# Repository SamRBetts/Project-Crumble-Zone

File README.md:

# Project-Crumble-Zone

Welcome to all version-controlled CAD for the ME capstone CanSat project!

Guidelines: 
<ul>
<li>Every assembly lives in a similarly-named folder containing itself + everything needed to construct it; this may include more assembly folders</li>
<li>Anything that is made from a single piece of material or single off-the-shelf component is a SLDPRT, anything else is a SLDASM</li>
<li>If you need a stock part, copy it or add it to the Github stock parts repo</li>
<li>Make subassemblies when a set of parts logically functions together; at minimum, anything that is glued together should be its own assembly, and anything that will be handled as a unit should be its own assembly (ex: the avbay should be one assembly) </li>
<li>File names should be snake case (like_this), folder names should be upper camel case (LikeThis)</li>
<li>Shared interface parts like couplers and screws should belong to the assembly that they are permanently attached to first; if it’s not obvious which side they should belong to, they should belong to the overarching assembly</li>
</ul>

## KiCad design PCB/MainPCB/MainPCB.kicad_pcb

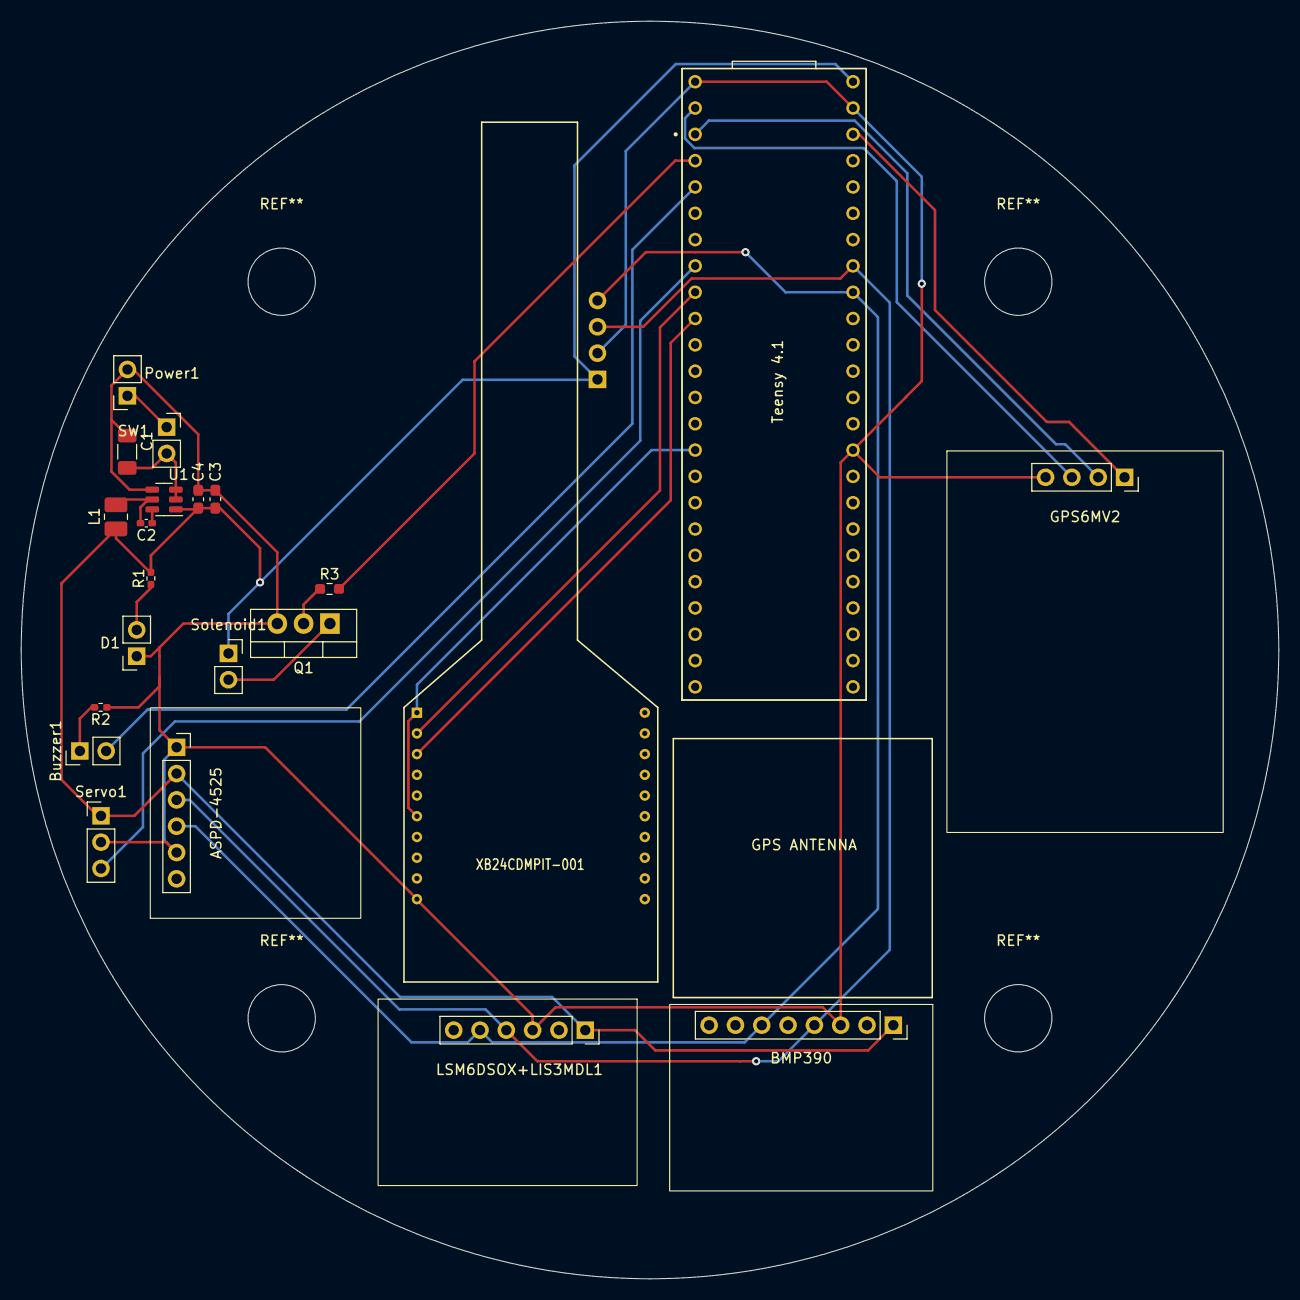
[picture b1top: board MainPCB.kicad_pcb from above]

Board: 2 copper layers, 121.4 x 121.4 mm, 23 parts (1 on the bottom side), 20 nets.

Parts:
ASPD-4525: Conn_01x06_Socket; PinSocket_1x06_P2.54mm_Vertical
BMP390: Conn_01x08_Socket; PinSocket_1x08_P2.54mm_Vertical
Buzzer1: Conn_01x02_Pin; PinHeader_1x02_P2.54mm_Vertical
C1: 10 uF; C_1206_3216Metric_Pad1.33x1.80mm_HandSolder
C2: 100 nF; C_0402_1005Metric_Pad0.74x0.62mm_HandSolder
C3, C4: 22 uF; C_0603_1608Metric_Pad1.08x0.95mm_HandSolder
D1: LED; PinSocket_1x02_P2.54mm_Vertical
GPS6MV2: Conn_01x04_Socket; PinSocket_1x04_P2.54mm_Vertical
L1: 4.7 uH; L_1008_2520Metric_Pad1.43x2.20mm_HandSolder
LSM6DSOX+LIS3MDL1: Conn_01x06_Socket; PinSocket_1x06_P2.54mm_Vertical
Power1: Conn_01x02_Pin; PinSocket_1x02_P2.54mm_Vertical
Q1: NMOS; TO-220-3_Vertical
R1: 100 kO; R_0402_1005Metric_Pad0.72x0.64mm_HandSolder
R2: 1 kO; R_0402_1005Metric_Pad0.72x0.64mm_HandSolder
R3: 2.1 kO; R_0603_1608Metric_Pad0.98x0.95mm_HandSolder
SEN291: Conn_01x04_Socket; PinSocket_1x04_P2.54mm_Vertical
SW1: SW_DIP_x01; PinSocket_1x02_P2.54mm_Vertical
Servo1: Conn_01x03_Pin; PinHeader_1x03_P2.54mm_Vertical
Solenoid1: Conn_01x02_Pin; PinSocket_1x02_P2.54mm_Vertical
TEENSY1: DEV-16771; MODULE_DEV-16771
U1: AP63205WU; TSOT-23-6
XBEE1: XB24CDMPIT-001; DIP-20

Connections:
+5V: ASPD-4525.2 (5V), BMP390.1 (VIN), C3.2, C4.2, L1.2, LSM6DSOX+LIS3MDL1.1 (Vin), R1.2, SEN291.1 (Vcc), Servo1.1, Solenoid1.1, TEENSY1.VIN, U1.1 (FB)
GND: ASPD-4525.1 (GND), ASPD-4525.5 (GND), BMP390.3 (GND), C1.2, C3.1, C4.1, D1.1 (K), GPS6MV2.4 (GND), LSM6DSOX+LIS3MDL1.3 (GND), Power1.2, Q1.3 (S), R2.1, SEN291.2 (GND), Servo1.2, TEENSY1.GND1 (GND), TEENSY1.GND2 (GND), TEENSY1.GND3 (GND), U1.4 (GND), XBEE1.10
unnamed: ASPD-4525.3 (SCL), BMP390.4 (SCL), LSM6DSOX+LIS3MDL1.4 (SCL), SEN291.3 (SCL), TEENSY1.19 (A5)
unnamed: ASPD-4525.4 (SDA), BMP390.6 (SDA), LSM6DSOX+LIS3MDL1.5 (SDA), SEN291.4 (SDA), TEENSY1.18 (A4)
unnamed: Buzzer1.1, R2.2
unnamed: Buzzer1.2, TEENSY1.3 (LRCLK2)
unnamed: D1.2 (A), R1.1
unnamed: GPS6MV2.2 (RX), TEENSY1.1 (TX1)
unnamed: GPS6MV2.3 (TX), TEENSY1.0 (RX1)
unnamed: GPS6MV2.1 (Vcc), TEENSY1.3.3V_1 (3.3V), TEENSY1.3.3V_2 (3.3V), XBEE1.1, XBEE1.6
unnamed: Power1.1, SW1.1
unnamed: Q1.1 (D), Solenoid1.2
unnamed: Q1.2 (G), R3.1
unnamed: Servo1.3, TEENSY1.6 (OUT1D)
unnamed: R3.2, TEENSY1.2 (OUT2)
unnamed: TEENSY1.7 (RX2), XBEE1.2
unnamed: TEENSY1.8 (TX2), XBEE1.3
unnamed: C2.1, U1.6 (BST)
unnamed: C1.1, SW1.2, U1.2 (EN), U1.3 (IN)
unnamed: C2.2, L1.1, U1.5 (SW)

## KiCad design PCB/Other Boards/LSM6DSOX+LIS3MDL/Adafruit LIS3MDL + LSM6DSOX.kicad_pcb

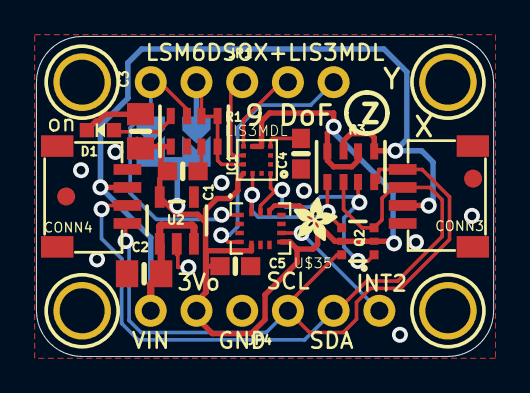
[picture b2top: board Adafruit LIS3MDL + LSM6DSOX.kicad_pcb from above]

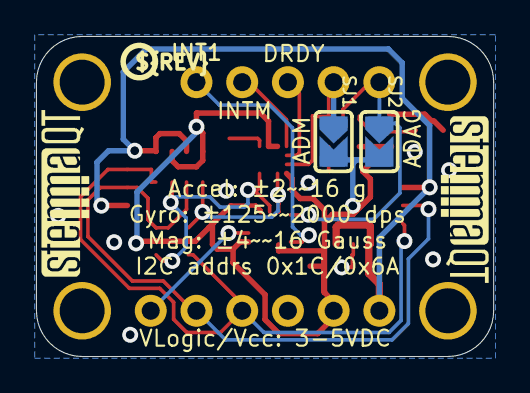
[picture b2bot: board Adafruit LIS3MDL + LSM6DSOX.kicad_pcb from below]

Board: 2 copper layers, 25.4 x 17.8 mm, 28 parts (5 on the bottom side), 15 nets.

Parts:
C1, C4: 0.1uF; 0603-NO
C2, C3: 10uF; 0805-NO
C5: 1uF; 0603-NO
CONN3, CONN4: STEMMA_I2C_QT; JST_SH4
D1: GREEN; CHIPLED_0603_NOOUTLINE
FID3, FID4: FIDUCIAL_1MM
IC1: LIS3MDL; LGA12_2X2MM
JP1: 1X05_ROUND_70
JP4: 1X06_ROUND_70
Q2: BSS138; SOT363
R1, R3: 10K; RESPACK_4X0603
SJ1, SJ2: SOLDERJUMPER_ARROW_NOPASTE
U2: AP2112K-3.3; SOT23-5
U$1, U$17, U$19, U$21: MOUNTINGHOLE2.5; MOUNTINGHOLE_2.5_PLATED
U$20: ADAFRUIT_2.5MM
U$25: PCBFEAT-REV-040
U$30, U$31: STEMMAQT
U$35: LSM6DSOX; LGA-14L

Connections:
3.3V: C1.1, C3.1, C5.1, IC1.5, IC1.6, IC1.10, JP4.2, Q2.2, Q2.5, R1.1, R3.2, R3.4, SJ1.2, SJ2.2, U2.5, U$35.5, U$35.8, U$35.12
ADAG: JP1.1, R1.7, SJ2.1, U$35.1
ADM: IC1.9, JP1.2, R1.4, R1.5, R1.6, SJ1.1
CAP: C4.1, IC1.4
DRDY: IC1.8, JP1.3
GND: C1.2, C2.2, C3.2, C4.2, C5.2, CONN3.1, CONN3.MT1, CONN3.MT2, CONN4.1, CONN4.MT1, CONN4.MT2, D1.C, IC1.2, IC1.3, IC1.12, JP4.3, R1.2, R1.3, U2.2, U$35.6, U$35.7
INT1: JP1.5, U$35.4
INT2: JP4.6, U$35.9
INTM: IC1.7, JP1.4
unnamed: D1.A, R1.8
SCL: CONN3.4, CONN4.4, JP4.4, Q2.6, R3.8
SCL_3V: IC1.1, Q2.1, R3.7, U$35.13
SDA: CONN3.3, CONN4.3, JP4.5, Q2.3, R3.6
SDA_3V: IC1.11, Q2.4, R3.5, U$35.14
VCC: C2.1, CONN3.2, CONN4.2, JP4.1, R3.1, R3.3, U2.1, U2.3

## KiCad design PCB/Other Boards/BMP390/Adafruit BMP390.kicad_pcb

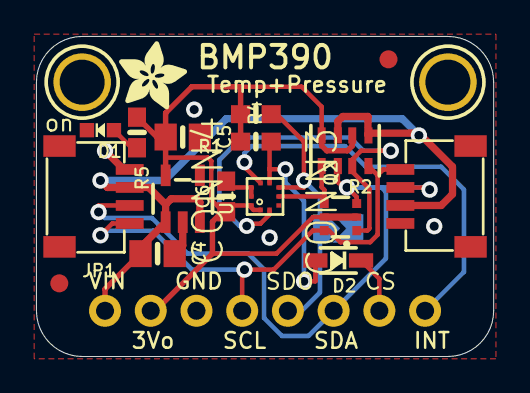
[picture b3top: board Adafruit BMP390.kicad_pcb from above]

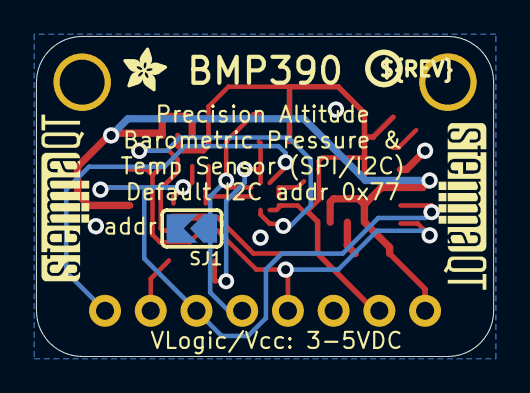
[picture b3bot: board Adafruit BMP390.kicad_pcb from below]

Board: 2 copper layers, 25.4 x 17.8 mm, 25 parts (5 on the bottom side), 12 nets.

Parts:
C4, C5: 10uF; 0805-NO
C6: 0.1uF; 0603-NO
CONN3, CONN4: STEMMA_I2C_QT; JST_SH4
D1: GREEN; CHIPLED_0603_NOOUTLINE
D2: 1N4148; SOD-323
FID3, FID4: FIDUCIAL_1MM
IC1: BMP388
JP1: 1X08_ROUND_70
Q2: BSS138; SOT363
R1, R4, R5: 10K; 0603-NO
R2: 10K; RESPACK_4X0603
SJ1: SOLDERJUMPER_ARROW_NOPASTE
U1: AP2112K-3.3; SOT23-5
U$2: ADAFRUIT_2.5MM
U$40, U$41: MOUNTINGHOLE2.5; MOUNTINGHOLE_2.5_PLATED
U$46: ADAFRUIT_3.5MM
U$47: PCBFEAT-REV-040
U$48, U$49: STEMMAQT

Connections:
3.3V: C5.1, C6.1, IC1.1, IC1.10, JP1.2, Q2.2, Q2.5, R1.2, R2.2, R2.4, R4.2, R5.1, U1.5
CS: D2.C, JP1.7
CS_3V: D2.A, IC1.6, R1.1
GND: C4.2, C5.2, C6.2, CONN3.1, CONN3.MT1, CONN3.MT2, CONN4.1, CONN4.MT1, CONN4.MT2, D1.C, IC1.3, IC1.8, IC1.9, JP1.3, SJ1.2, U1.2
INT: IC1.7, JP1.8
unnamed: D1.A, R5.2
SCK/SCL: CONN3.4, CONN4.4, JP1.4, Q2.6, R2.8
SCK_3V: IC1.2, Q2.1, R2.7
SDI/SDA: CONN3.3, CONN4.3, JP1.6, Q2.3, R2.6
SDI_3V: IC1.4, Q2.4, R2.5
SDO/ADR: IC1.5, JP1.5, R4.1, SJ1.1
VCC: C4.1, CONN3.2, CONN4.2, JP1.1, R2.1, R2.3, U1.1, U1.3

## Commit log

2023-10-04 Update README.md
    updated formatting guidelines
2023-10-04 Nose cone as heat shield design CAD
2023-10-09 Container with Servo Casing
2023-10-09 concept 1 body
2023-10-09 Slitv2assem unfinished
2023-10-09 slitv2 finished
2023-10-10 more concepts
2023-10-10 update concept 1
2023-10-10 added colors
2023-10-10 Final slit design for external review
2023-10-10 System Diagram Edits
2023-10-11 Nose Cone Changes
2023-10-11 new working folder and design dashboard
2023-10-13 Made Ribcage
2023-10-13 initial code setup
2023-10-13 Ready for component addition
2023-10-17 Prototype Telemetry Screen complete
    V0 - all graphs included and all required data with placeholders
2023-10-17 sensor / equipment comments
2023-10-18 Something?? idk
2023-10-18 hewwo
2023-10-18 Teensy 4.1 CAD
2023-10-18 NEO-6M GPS CAD
2023-10-18 Added sensor CAD
    Added barometer, accelerometer, backup camera, and RunCam files
2023-10-18 XBee CAD
2023-10-18 Pitot tube
2023-10-18 Matek Airspeed Sensor
2023-10-18 Pressure and Accelerometer
2023-10-18 Added FSW folder
2023-10-18 fixing folders
2023-10-20 now defunct edits
2023-10-20 Added Bulkhead
2023-10-20 Bulkhead update
2023-10-22 Began structure v2
2023-10-24 Example of realtime plotting with given pressure data
    an example of relevant real-time plotting with given pressure data.
2023-10-24 initial shell
2023-10-24 add egg shell to structure
2023-10-24 made a test layout assem
    also converted a bunch of parts to 2023
2023-10-24 pancake layout test
2023-10-24 new runcam
    old runcam file was corrupted. fixed it and added it to working model
2023-10-25 added prelim pancake
    also started remodeling BMP390
2023-10-25 BMP390 SLDPRT completed
2023-10-25 added antenna model
2023-10-25 Added Nose Skeleton
2023-10-27 threads and o ring
2023-10-27 Added more rods
2023-10-27 Made Latch Arm
2023-10-27 Latch Placed in Assembly
2023-10-27 Added nose cone
2023-10-27 smaller better shell
2023-10-27 revision of caudal slits
2023-10-28 parachute v2 assem update
2023-10-30 v2 parachute update
2023-11-01 added deployable struts
    Added prototype deployable struts
2023-11-01 uh...idk
2023-11-01 airspeed sensor code
2023-11-01 Removed Components from structure assem
2023-11-01 moved electronics to dedicated subassembly
2023-11-01 moved pancake to electronics folder
    organization babey. we can move it back later if we need
2023-11-01 Sorta added pitot tube
2023-11-03 parachute cont. volume update :3
2023-11-03 Assembly Updates
2023-11-03 Added subassemblies to FullAssem
2023-11-03 mounting
2023-11-03 egg shell mounted to full assembly
2023-11-03 Changed cansat length
2023-11-03 updated design docs
2023-11-03 testing
2023-11-03 uh...something?
2023-11-05 normal updates
2023-11-05 Fixed Egg Shell
2023-11-05 Changed length of body
2023-11-05 fixed electronics positions
2023-11-05 new latch added to nose cone
2023-11-06 omfg these arms were way more trouble than I anticipated
2023-11-06 double check push
2023-11-06 redo for sam
2023-11-06 should be fixed
2023-11-06 more parachute stuff
2023-11-06 Added stowed and deployed skirts
    note they are two separate parts because I'm a baby
2023-11-06 changed some colors
2023-11-06 Revert "Merge branch 'main' of https://github.com/SamRBetts/Project-Crumple-Zone"
    This reverts commit b4e70f6994341812c360d4cb150c0f566dacbcf3, reversing
    changes made to 39e4297591490ef4596a126c9db5a74489ab4964.
2023-11-06 ParaAssem
2023-11-06 Added para assm
    not fully defined yet
2023-11-07 new slit design
2023-11-07 revamped pancake. added headers
2023-11-07 hopefully updated electronics pancake dims
2023-11-07 fixed antenna + mates in full assembly
    by fixing it the antenna i mean it no longer works like it should (is no longer limited to 0-90 deg) but also is no longer broken (does not clip through objects)
2023-11-07 new parachute box added
    also changed some colors ;]
2023-11-07 beeg nose
2023-11-07 oops??
2023-11-08 graphics changes
2023-11-08 Update TelemetryScreenProto.py
    made telemetry screen
2023-11-29 Nose cone edits and slight fixes
2023-11-29 linking nose cone to spreadsheet
2023-11-29 new egg holder
2023-11-29 deleted spreadsheet testing files with the silly names
2023-11-29 Added locking pin
2023-11-29 update egg holder with spreadsheet
2023-11-29 Added pseudocode for GS software
    all (hopefully) class definitions and descriptions exist
2023-12-04 Small edits, added screws to nose cone
2023-12-04 Springs are very real and I very hate them. they work now.
2023-12-06 Finished pseudo code, started csv handling
2023-12-06 finalized egg protection, updated assembly
2023-12-06 Arm Wheel Testing Versions
2023-12-06 Can append packet to csv file and save it!
2023-12-06 Folder Organization
2023-12-06 Para V3
2023-12-06 add new shell
2023-12-06 Assem update w/ v3 para
2023-12-06 New diameter just dropped
2023-12-06 updated electronics board and egg holder with new diameters
2023-12-06 Update to para v3 for smaller diameter; idk why full assem gets mad at me but it is what it is
2023-12-06 minor assem edits, added arm wheel fillet
2023-12-06 created dictionary for telemetry points, started cmdhelper class, and created splice packet method
2023-12-08 updated tolerances for para v3 plus new more accurate dims
2023-12-11 Finished CMDHelper, added function to packethelper, started xbeehandler
    PySerial library ftw
2023-12-11 shell stuff
2023-12-12 testing configuration for nose cone
2023-12-12 update v3
2023-12-12 Meager updates to arm wheel
2023-12-13 Assembly fixes, nose cone diameter edit
2023-12-13 New pitot holder started
2023-12-13 made spacers
2023-12-13 made spacers flexible, added to full assem
2023-12-13 Redesigned pitot tube support stucture
2023-12-13 Re-added structure to fullassem
2023-12-13 vaguely fixed some mates
2023-12-14 para v4 yay
2023-12-19 v4 i guess
2023-12-19 made an oopsy
2023-12-19 made egg protection stls for printing
2023-12-19 spacer stls
2023-12-20 eps cad
2023-12-20 voltage regulator
2023-12-20 new egg protections
2023-12-20 Tolerance edits, started working on gears
2023-12-20 Edited a bunch of things
    added dynamic plotting to graph,
    fixed telemetry screen
    added command buttons
2024-01-08 Dynamic random telemetry screen almost finished!
    Still need to fix legend and add command buttons
2024-01-09 Dynamic Telemetry screen done!
2024-01-09 V2 is now static in time - i will no longer be changing it
    for demo only
2024-01-09 flight software integration
2024-01-10 moved covers, edited egg shell
2024-01-16 add dxf's of bulkheads
2024-01-16 electornic pancake dxf
2024-01-17 Xbee integrated in dynamic GUI!
2024-01-17 parabox update plus basic test code
2024-01-19 update to parabox cause i'm an idiot
2024-01-29 egg shell
2024-01-30 implemented command sending
2024-01-30 Added a dummy assembly to do weird designs to, added rocket body model and assem using it, made alternate designs, changed tolerances, made dimension drawings
2024-01-31 this is not a folder of honor.
2024-01-31 eggand stuff and assembly
2024-01-31 fired shots at the old assembly
2024-01-31 parabox stuff i guess
2024-01-31 added screws to old assem mockup
2024-01-31 added second design for egg protetction
2024-01-31 Added leg configuration
2024-01-31 tried to make heat shield presentable
    failed. assembly is broken a little bit
2024-01-31 Added Battery Holder
2024-01-31 configurations, parachute box, colors
    tenuously fixed the skirt stowing issue (switch configurations back and forth while while suppressing and suppressing the skirt parts, it'll work eventually). fixed parachute can/nut mates to avoid c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
2024-01-31 idek what i did
2024-01-31 i be adddddiiiin lots of stuff i froget what i changed lmao
    hahahahahahahahaha
2024-02-05 Implemented simulation mode
    Still needs to be tested in loop with xbee
2024-02-06 aha i be doin work
    hi
2024-02-07 some jank, presumably
2024-02-07 created skirt attachment pieces and their stl's
2024-02-07 state machine works with simulation mode wowwowow
2024-02-07 updated bulkhead dxf's
2024-02-07 Edits to nose cone
2024-02-11 Assembly fixes, added gear tooth profile to latches
2024-02-12 parabox new update part 1 idk
2024-02-14 code broke i fix it
    pls be careful when committing!!!!!
2024-02-14 continuous servo implementation
    hopefully it work
2024-02-14 r2d2 parabox crying emoji
2024-03-06 made pattern for cutting and sewing skirt panels
2024-03-06 Added plots resets, changed some commands, small edits
    Separated Telemetry Screen and Button/display labels into a different class
2024-03-06 Updated docs, cleaned up files, added icon
2024-03-06 created runcam frame
2024-03-13 PCB. 'Tis done.
2024-03-13 Shell fixes
2024-03-13 STLs for eggs
2024-03-13 Added space for springs in nose cone, gerber files for PCB.
2024-03-13 added eyebolt hole to bulkhead, ran an FEA on it for stress
2024-03-13 battery holder
2024-03-13 created new camera holder
2024-03-19 Nose Cone Fixes
2024-03-20 Nose cone fixes for better pins
2024-03-20 updated cam holder, added to assem, and fixed eggshell+full mates
2024-03-20 changed runcam strut holes from 2 to 1, added parabox v5 to assem
2024-03-20 made stl of updated cam holder
2024-03-20 Color changes
2024-03-24 updated model for parabox
2024-03-27 small telemetry screen updates
2024-03-31 slimmed spacers by 1/3, added prelim top bulkplate slimming
2024-03-31 slimmed pitot tube holder
    thinned the wall interface with sheet metal to 4mm on each side
2024-03-31 cut worm gear
2024-03-31 i mighta broke the spacers
    help
2024-03-31 yay smol pbox
2024-04-01 Slimmed pitot mount, manuf. edits to pin
2024-04-01 Added drawing for heat shield pin
2024-04-01 added pbox to assm, added cut bottom bulkplate
2024-04-01 pbox small changes
2024-04-02 fixed spacers
2024-04-02 processor resets
2024-04-02 new servo
2024-04-02 stls of spacers
2024-04-02 updated bottom bulkhead for strength
2024-04-03 exported dxf of egg shell mount, made a bit thicker
2024-04-03 new dxf hehe
2024-04-03 Heat shield pin drawings, new nosecone STL
2024-04-03 Mate Updates
2024-04-03 bulkhead switch location
2024-04-03 pb fit adjustments
2024-04-03 Fixed mate spaghetti. Added flares to nose cone latches
2024-04-03 modified servo mount
    I made it so servo mount has enough clearance for shaft coupler. Still need to add mounting holes into the bulkhead!
2024-04-03 servo mount modification
    added clearance so the mount doesn't hit servo coupler. still need correct mounting holes!
2024-04-03 Fixed Assem Again
2024-04-16 updated bulkplates
2024-04-17 bulkhead and parabox holes
2024-04-18 Added servo mount, finalized bulkheads
2024-04-23 two switch cover designs
2024-04-24 updated bulkhead thickness, new spacer stl's
2024-04-24 i got vscode to work
2024-04-24 Added screws, a couple STLs, FIXED GITIGNORE YIPPEE!!
2024-04-24 gitignore
2024-04-24 Revert "Merge branch 'main' of https://github.com/SamRBetts/Project-Crumple-Zone"
    This reverts commit 9fbe9ea6ac6346b95b4d28350bf809624853997b, reversing
    changes made to 0e837c4f8085b2eeeb44ed911fa2023abd4ecf08.
2024-04-24 idek
2024-04-24 detatch test command, servo kinda working
2024-04-27 new servo commands
2024-04-30 solenoid extends 100 ms after it retracts
2024-04-30 airspeed sensor error
2024-05-01 added a test command screen, fixed telemetry recieving
2024-05-08 thicker hinge
2024-05-08 magnetometer mostly calibrated
